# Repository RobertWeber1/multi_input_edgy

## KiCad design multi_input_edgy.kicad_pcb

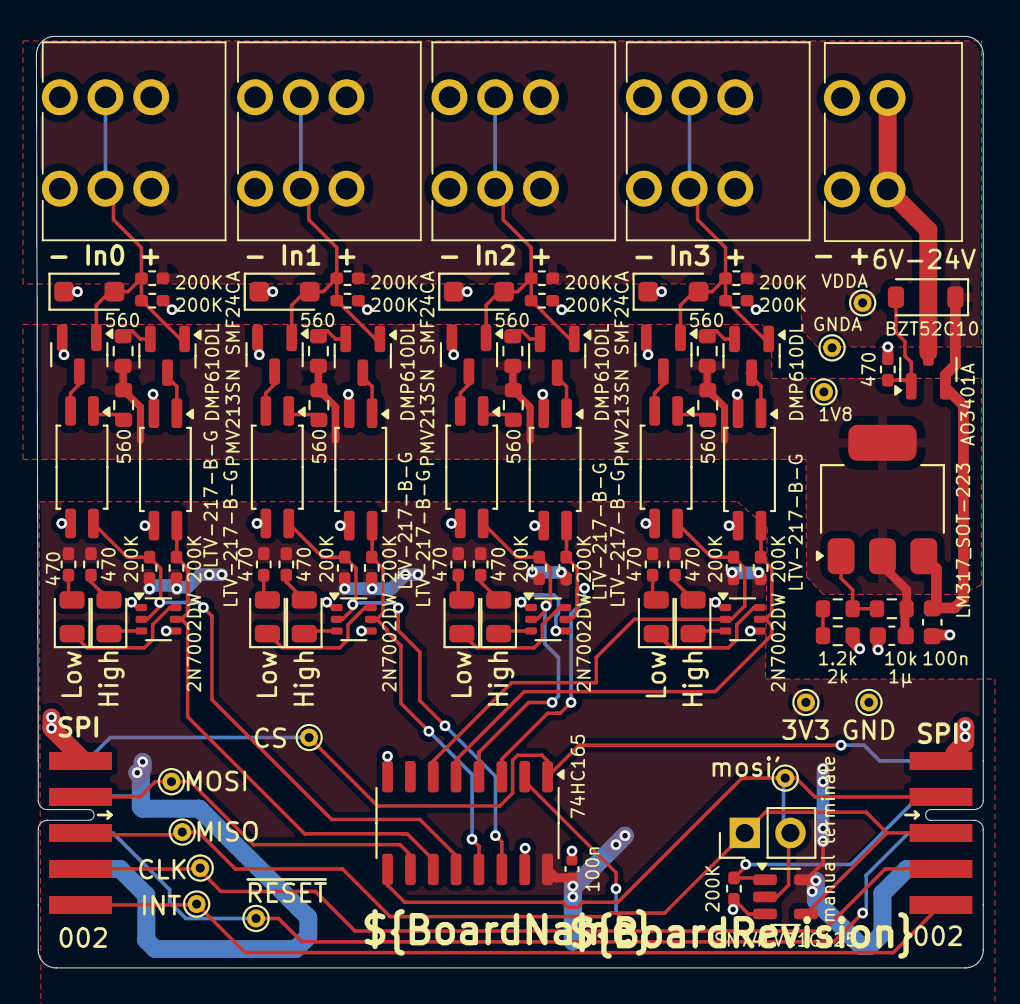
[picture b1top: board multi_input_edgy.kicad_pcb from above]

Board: 2 copper layers, 52.6 x 51.8 mm, 97 parts (0 on the bottom side), 61 nets.

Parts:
C1: 100n; C_0402_1005Metric
C9: 100n; C_0603_1608Metric
C10: 1µ; C_0603_1608Metric
D1, D4, D7, D10: SMF24CA; D_SOD-123F
D2, D5, D8, D11: KT-0805Y (orange-red) Vf=2.0V; LED_0805_2012Metric
D3, D6, D9, D12: KT-0805G (emerald) Vf=2.8V; LED_0805_2012Metric
D13: BZT52C10; D_SOD-123
J1: 002; on_edge_2x05_device
J2: 002; on_edge_2x05_host
J3: - In1 +; KF141V-2.54-3P
J4: - In2 +; KF141V-2.54-3P
J5: - In0 +; KF141V-2.54-3P
J6: - In3 +; KF141V-2.54-3P
J7: 6V-24V; KF141V-2.54-2P
JP1: manual terminate; PinHeader_1x02_P2.54mm_Vertical
Q1, Q5, Q9, Q13: PMV213SN; SOT-23
Q2, Q6, Q10, Q14: DMP610DL; SOT-23
Q3, Q7, Q11, Q15: 2N7002DW; SOT-363_SC-70-6
Q17: AO3401A; SOT-23
R1, R2, R3, R4, R5, R8, R9, R10, R11, R14, R15, R16, R17, R20, R21, R22, R23: 200K; R_0402_1005Metric_Pad0.72x0.64mm_HandSolder
R6, R7, R12, R13, R18, R19, R24, R25, R28: 470; R_0402_1005Metric_Pad0.72x0.64mm_HandSolder
R26: 10k; R_0603_1608Metric
R27: 1.2k; R_0603_1608Metric
R29: 2k; R_0603_1608Metric
R30, R31, R32, R33, R34, R35, R36, R37: 560; R_0603_1608Metric
TP6: MOSI; TestPoint_THTPad_D1.0mm_Drill0.5mm
TP7: CLK; TestPoint_THTPad_D1.0mm_Drill0.5mm
TP8: INT; TestPoint_THTPad_D1.0mm_Drill0.5mm
TP9: ~{RESET}; TestPoint_THTPad_D1.0mm_Drill0.5mm
TP10: MISO; TestPoint_THTPad_D1.0mm_Drill0.5mm
TP11: mosi'; TestPoint_THTPad_D1.0mm_Drill0.5mm
TP12: CS; TestPoint_THTPad_D1.0mm_Drill0.5mm
TP13: 3V3; TestPoint_THTPad_D1.0mm_Drill0.5mm
TP14: GND; TestPoint_THTPad_D1.0mm_Drill0.5mm
TP15: VDDA; TestPoint_THTPad_D1.0mm_Drill0.5mm
TP16: GNDA; TestPoint_THTPad_D1.0mm_Drill0.5mm
TP17: 1V8; TestPoint_THTPad_D1.0mm_Drill0.5mm
U1: SN74LVC1G125; SOT-23-5
U2: 74HC165; SO-16_3.9x9.9mm_P1.27mm
U3, U4, U5, U6, U7, U8, U9, U10: LTV-217-B-G; SSOP-4_4.4x2.6mm_P1.27mm
U12: LM317_SOT-223; SOT-223-3_TabPin2

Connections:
+1V8: C10.2, R26.1, R30.1, R31.1, R32.1, R33.1, R34.1, R35.1, R36.1, R37.1, TP17.1, U12.2 (VO)
+3V3: C1.1, J1.7 (status), J1.9 (3.3V), J2.9 (3.3V), R4.1, R5.1, R6.1, R7.1, R10.1, R11.1, R12.1, R13.1, R16.1, R17.1, R18.1, R19.1, R22.1, R23.1, R24.1, R25.1, TP13.1, U1.5 (VCC), U2.16 (VCC)
/4xInput/CLK: J1.4 (SCLK), J2.4 (SCLK), TP7.1, U2.2 (CP)
/4xInput/CS: J1.6 (CS), J2.6 (CS), TP12.1, U2.1 (~PL)
/4xInput/In0/In0_high: Q11.5 (G), R17.2, U2.11 (D0), U8.4 (R)
/4xInput/In0/In0_low: Q11.2 (G), R16.2, U2.12 (D1), U7.4 (R)
/4xInput/In1/In1_high: Q3.5 (G), R5.2, U2.13 (D2), U4.4 (R)
/4xInput/In1/In1_low: Q3.2 (G), R4.2, U2.14 (D3), U3.4 (R)
/4xInput/In2/In2_high: Q7.5 (G), R11.2, U2.3 (D4), U6.4 (R)
/4xInput/In2/In2_low: Q7.2 (G), R10.2, U2.4 (D5), U5.4 (R)
/4xInput/In3/In3_high: Q15.5 (G), R23.2, U2.5 (D6), U10.4 (R)
/4xInput/In3/In3_low: Q15.2 (G), R22.2, U2.6 (D7), U9.4 (R)
/4xInput/MOSI: J1.2 (MOSI), TP6.1, U2.10 (DS)
/MOSI': J2.2 (MOSI), JP1.2 (B), TP11.1, U1.2, U2.9 (Q7)
/downstream_status: J2.7 (status), R1.1, U1.1
/upstream_miso: J1.3 (MISO), J2.3 (MISO), JP1.1 (A), TP10.1, U1.4
GND: C1.2, J1.1 (GND), J2.1 (GND), Q3.1 (S), Q3.4 (S), Q7.1 (S), Q7.4 (S), Q11.1 (S), Q11.4 (S), Q15.1 (S), Q15.4 (S), R1.2, TP14.1, U1.3 (GND), U2.8 (GND), U2.15 (~CE), U3.3 (R), U4.3 (R), U5.3 (R), U6.3 (R), U7.3 (R), U8.3 (R), U9.3 (R), U10.3 (R)
GNDA: C9.1, C10.1, D1.1 (A1), D4.1 (A1), D7.1 (A1), D10.1 (A1), J3.1, J4.1, J5.1, J6.1, J7.1, Q1.2 (S), Q5.2 (S), Q9.2 (S), Q13.2 (S), R3.2, R9.2, R15.2, R21.2, R28.2, R29.2, TP16.1, U4.2 (K), U6.2 (K), U8.2 (K), U10.2 (K)
unnamed: D1.2 (A2), J3.2, Q1.1 (G), Q2.1 (G), R2.2, R3.1
unnamed: D2.2 (A), R6.2
unnamed: D2.1 (K), Q3.6 (D)
unnamed: D3.2 (A), R7.2
unnamed: D3.1 (K), Q3.3 (D)
unnamed: D4.2 (A2), J4.2, Q5.1 (G), Q6.1 (G), R8.2, R9.1
unnamed: D5.2 (A), R12.2
unnamed: D5.1 (K), Q7.6 (D)
unnamed: D6.2 (A), R13.2
unnamed: D6.1 (K), Q7.3 (D)
unnamed: D7.2 (A2), J5.2, Q9.1 (G), Q10.1 (G), R14.2, R15.1
unnamed: D8.2 (A), R18.2
unnamed: D8.1 (K), Q11.6 (D)
unnamed: D9.2 (A), R19.2
unnamed: D9.1 (K), Q11.3 (D)
unnamed: D10.2 (A2), J6.2, Q13.1 (G), Q14.1 (G), R20.2, R21.1
unnamed: D11.2 (A), R24.2
unnamed: D11.1 (K), Q15.6 (D)
unnamed: D12.2 (A), R25.2
unnamed: D12.1 (K), Q15.3 (D)
unnamed: D13.2 (A), Q17.1 (G), R28.1
unnamed: J1.5 (INT), J2.5 (INT), TP8.1
unnamed: J1.8 (~RESET), J2.8 (~RESET), TP9.1
unnamed: Q1.3 (D), U3.2 (K)
unnamed: Q2.3 (D), U4.1 (A)
unnamed: Q2.2 (S), R34.2
unnamed: Q5.3 (D), U5.2 (K)
unnamed: Q6.3 (D), U6.1 (A)
unnamed: Q6.2 (S), R35.2
unnamed: Q9.3 (D), U7.2 (K)
unnamed: Q10.3 (D), U8.1 (A)
unnamed: Q10.2 (S), R36.2
unnamed: Q13.3 (D), U9.2 (K)
unnamed: Q14.3 (D), U10.1 (A)
unnamed: Q14.2 (S), R37.2
unnamed: R27.2, R29.1
unnamed: R30.2, U3.1 (A)
unnamed: R31.2, U5.1 (A)
unnamed: R32.2, U7.1 (A)
unnamed: R33.2, U9.1 (A)
unnamed: R26.2, R27.1, U12.1 (ADJ)
VDDA: C9.2, D13.1 (K), J3.3, J4.3, J5.3, J6.3, Q17.2 (S), R2.1, R8.1, R14.1, R20.1, TP15.1, U12.3 (VI)
VDD_EXT: J7.2, Q17.3 (D)

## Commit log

2024-11-11 V1.0
2024-11-11 Add schematic and 3d image of board
2024-11-11 Fix constant current source (AL5809) symbol and footprint
2024-11-11 Get board name and version from text variable
2024-11-17 Add pre-commit hooks to generate schematic pdf and board rendering
2025-10-19 Change optocouplers, improve power routing
